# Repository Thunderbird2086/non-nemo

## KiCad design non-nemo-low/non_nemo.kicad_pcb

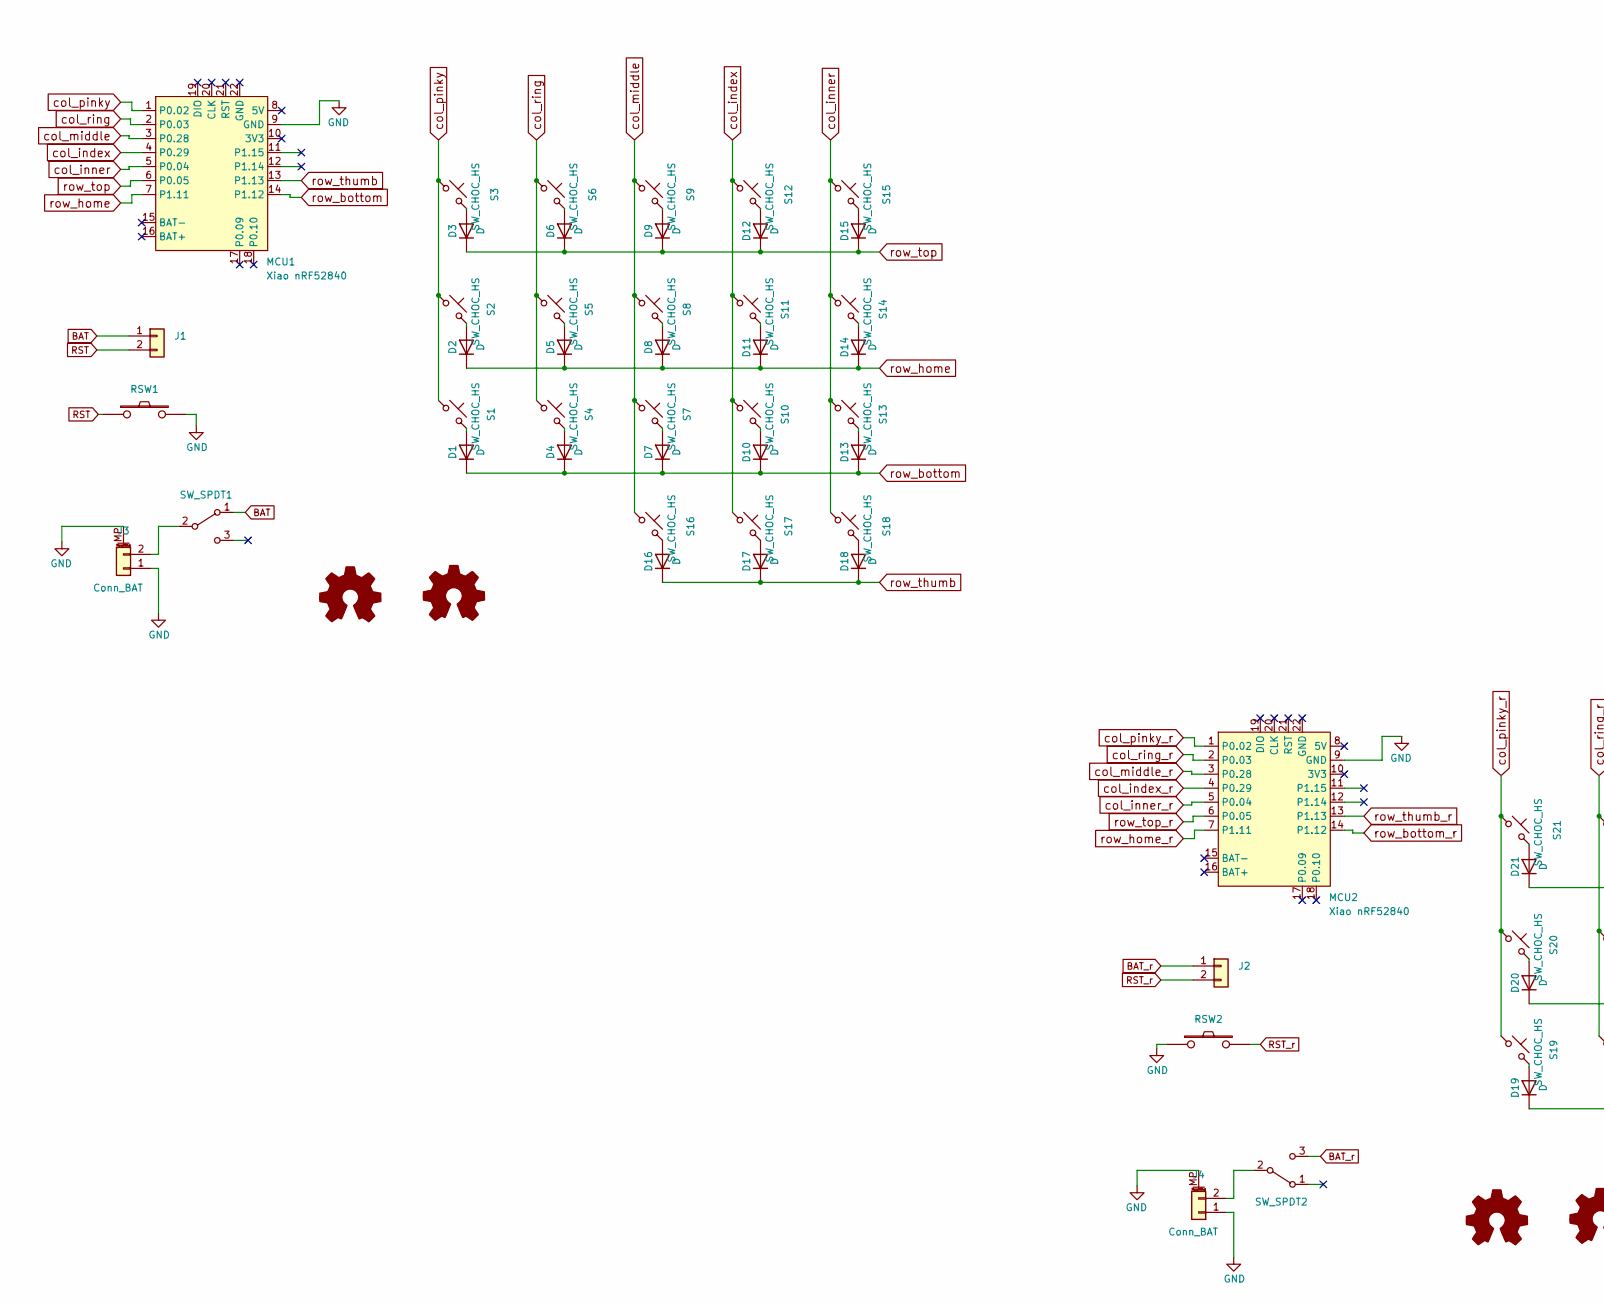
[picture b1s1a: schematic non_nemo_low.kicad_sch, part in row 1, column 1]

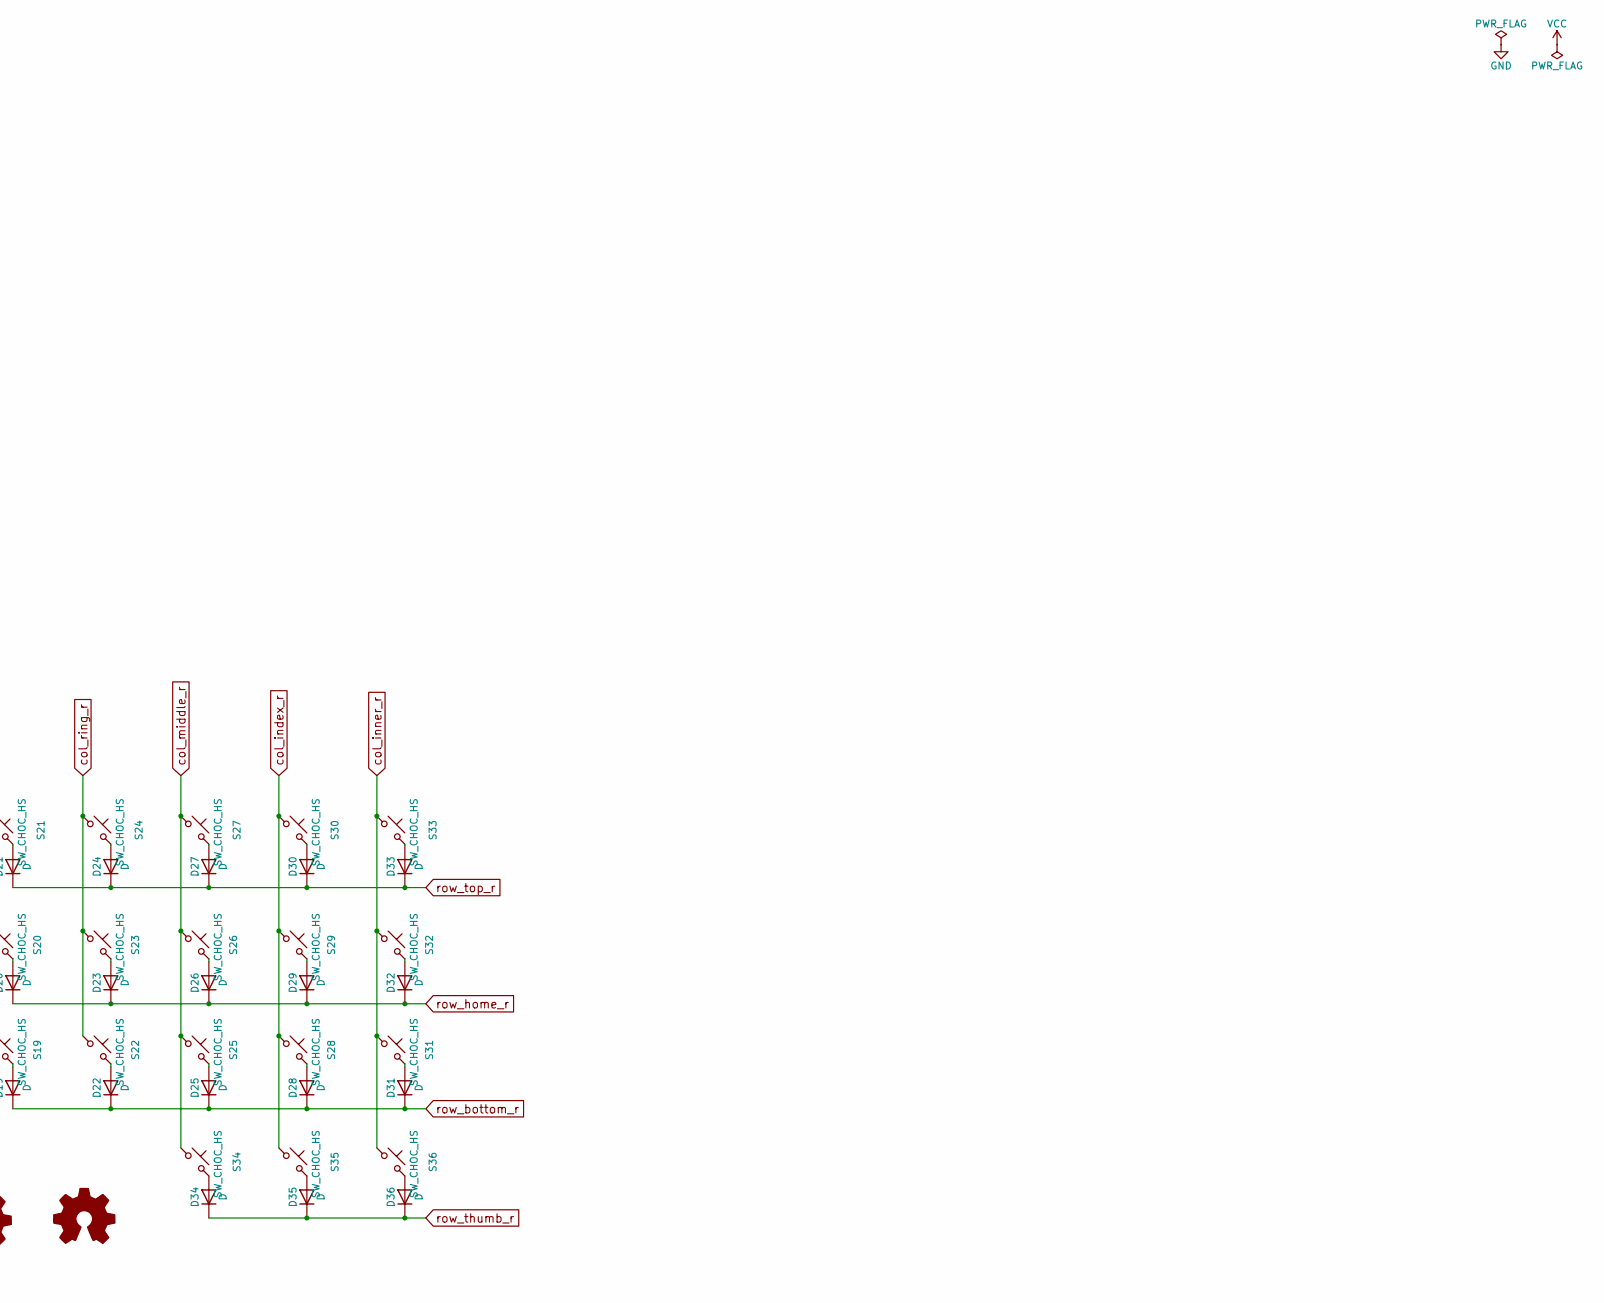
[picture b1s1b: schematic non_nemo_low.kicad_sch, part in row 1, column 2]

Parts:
D1, D2, D3, D4, D5, D6, D7, D8, D9, D10, D11, D12, D13, D14, D15, D16, D17, D18, D19, D20, D21, D22, D23, D24, D25, D26, D27, D28, D29, D30, D31, D32, D33, D34, D35, D36: D; D3_SMD
J1, J2: Conn_01x02; Tag_Pogopin_1x02_P2.54mm
J3, J4: Conn_BAT; Molex_Pico-EZmate_78171-0002_1x02-1MP_P1.20mm_HandSolder
LOGO1, LOGO3: Logo_Open_ErgoGen; utility_ergogen_logo
LOGO2, LOGO4: Logo_Open_Hardware_Small; OSHW-Logo_5.7x6mm_SilkScreen
MCU1, MCU2: Xiao nRF52840; Xiao_nRF52840_edgecut
RSW1, RSW2: SMT 2X4X3.5MM Tactile Tact Push Button
S1, S2, S3, S4, S5, S6, S7, S8, S9, S10, S11, S12, S13, S14, S15, S16, S17, S19, S20, S21, S22, S23, S24, S25, S26, S27, S28, S29, S30, S31, S32, S33, S34, S35: SW_CHOC_HS; SW_choc_v1_v2_HS_1u
S18, S36: SW_CHOC_HS; SW_choc_v1_v2_HS_1.5u
SW_SPDT1: SW_SPDT1; SW_SPDT_PCM12
SW_SPDT2: SW_SPDT2; SW_SPDT_PCM12

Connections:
unnamed: D1.2 (A), S1.1
unnamed: D2.2 (A), S2.1
unnamed: D3.2 (A), S3.1
unnamed: D4.2 (A), S4.1
unnamed: D5.2 (A), S5.1
unnamed: D6.2 (A), S6.1
unnamed: D7.2 (A), S7.1
unnamed: D8.2 (A), S8.1
unnamed: D9.2 (A), S9.1
unnamed: D10.2 (A), S10.1
unnamed: D11.2 (A), S11.1
unnamed: D12.2 (A), S12.1
unnamed: D13.2 (A), S13.1
unnamed: D14.2 (A), S14.1
unnamed: D15.2 (A), S15.1
unnamed: D16.2 (A), S16.1
unnamed: D17.2 (A), S17.1
unnamed: D18.2 (A), S18.1
unnamed: D19.2 (A), S19.1
unnamed: D20.2 (A), S20.1
unnamed: D21.2 (A), S21.1
unnamed: D22.2 (A), S22.1
unnamed: D23.2 (A), S23.1
unnamed: D24.2 (A), S24.1
unnamed: D25.2 (A), S25.1
unnamed: D26.2 (A), S26.1
unnamed: D27.2 (A), S27.1
unnamed: D28.2 (A), S28.1
unnamed: D29.2 (A), S29.1
unnamed: D30.2 (A), S30.1
unnamed: D31.2 (A), S31.1
unnamed: D32.2 (A), S32.1
unnamed: D33.2 (A), S33.1
unnamed: D34.2 (A), S34.1
unnamed: D35.2 (A), S35.1
unnamed: D36.2 (A), S36.1
unnamed: J1.2, J3.2, RSW1.1, SW_SPDT1.2 (B)
unnamed: J2.2, J4.2, RSW2.2, SW_SPDT2.2 (B)
col_index: MCU1.4 (P0.29), S10.2, S11.2, S12.2, S17.2
col_index_r: MCU2.4 (P0.29), S28.2, S29.2, S30.2, S35.2
col_inner: MCU1.5 (P0.04), S13.2, S14.2, S15.2, S18.2
col_inner_r: MCU2.5 (P0.04), S31.2, S32.2, S33.2, S36.2
col_middle: MCU1.3 (P0.28), S7.2, S8.2, S9.2, S16.2
col_middle_r: MCU2.3 (P0.28), S25.2, S26.2, S27.2, S34.2
col_pinky: MCU1.1 (P0.02), S1.2, S2.2, S3.2
col_pinky_r: MCU2.1 (P0.02), S19.2, S20.2, S21.2
col_ring: MCU1.2 (P0.03), S4.2, S5.2, S6.2
col_ring_r: MCU2.2 (P0.03), S22.2, S23.2, S24.2
row_bottom: D1.1 (K), D4.1 (K), D7.1 (K), D10.1 (K), D13.1 (K), MCU1.14 (P1.12)
row_bottom_r: D19.1 (K), D22.1 (K), D25.1 (K), D28.1 (K), D31.1 (K), MCU2.14 (P1.12)
row_home: D2.1 (K), D5.1 (K), D8.1 (K), D11.1 (K), D14.1 (K), MCU1.7 (P1.11)
row_home_r: D20.1 (K), D23.1 (K), D26.1 (K), D29.1 (K), D32.1 (K), MCU2.7 (P1.11)
row_thumb: D16.1 (K), D17.1 (K), D18.1 (K), MCU1.13 (P1.13)
row_thumb_r: D34.1 (K), D35.1 (K), D36.1 (K), MCU2.13 (P1.13)
row_top: D3.1 (K), D6.1 (K), D9.1 (K), D12.1 (K), D15.1 (K), MCU1.6 (P0.05)
row_top_r: D21.1 (K), D24.1 (K), D27.1 (K), D30.1 (K), D33.1 (K), MCU2.6 (P0.05)

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
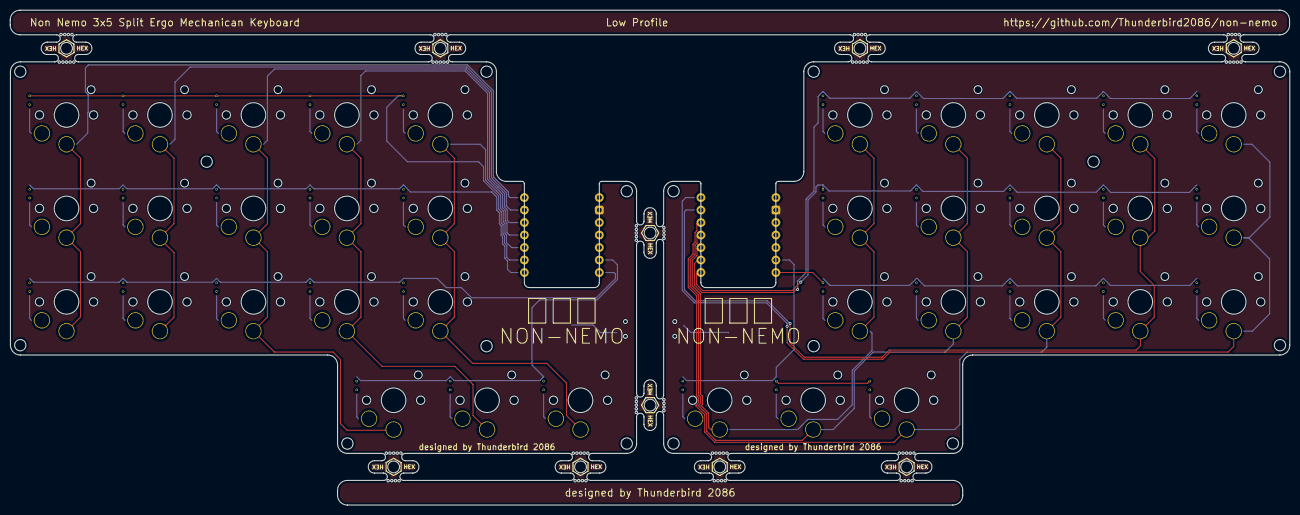
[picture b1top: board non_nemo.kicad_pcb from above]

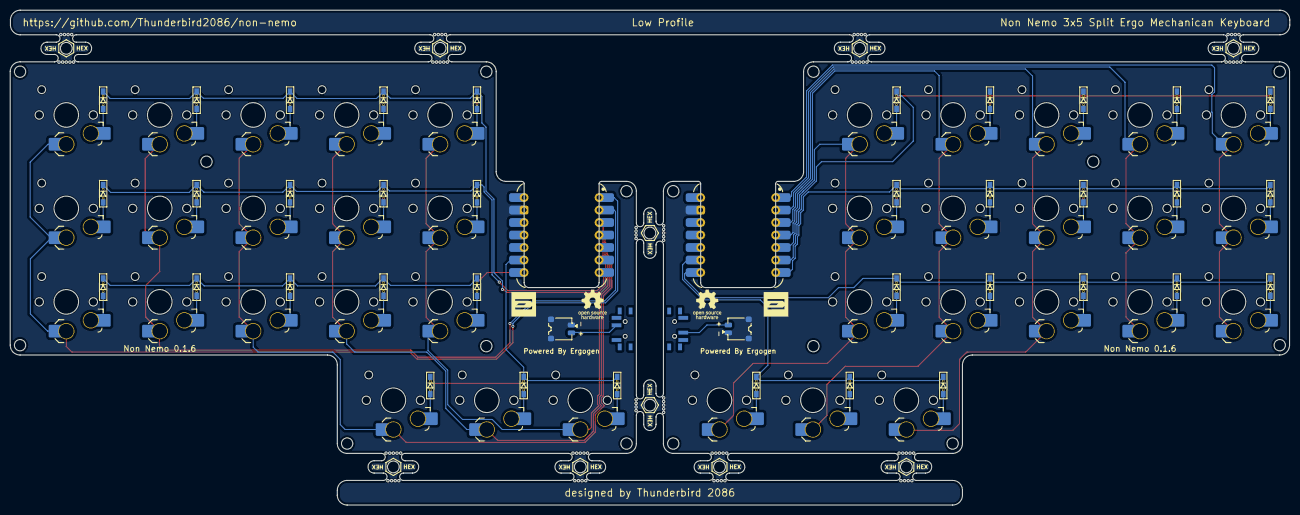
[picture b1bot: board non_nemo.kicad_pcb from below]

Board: 2 copper layers, 260.1 x 100.6 mm, 92 parts (2 on the bottom side), 57 nets.

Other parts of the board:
X1, X2, X3, X4, X5, X6, X7, X8, X9, X10: 5.5mm; mousebites_5p5mm_easysnap
